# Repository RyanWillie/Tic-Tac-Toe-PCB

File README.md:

# Tic-Tac-Toe-PCB

A continuation of my Hobby PCB designs is the arduino based Tic Tac Toe circuit, utilising some surface mount components this circuit was aimed to give some practical experience in implementing a microcontroller from scratch utilising the reference design sheets. Using multiplexing each grid is able to light up with an X or a O to indicate who has claimed the tile.

## Component Selection

The main principle of the component selection was to use readily available components with libraries available for easy and quick setup,as well as preferring breakout boards so that the components can be easily salvaged/replaced for other projects when it is not needed. Therefore the microcontroller will be an Arduino nano, and the popular NRF24L01 transciever as the available libary makes connection extremely easy.

## BOM
  - Arduino Nano
  - 72x LED
  - 9 x Switches
  - Crystal
  - Capacitors
  
## Proof of Concept
 No proof of concept was able to be created for this circuit due to the required components that were not on hand.

## PCB Design and Manufacturing

The open source program KiCad was used as the design software for the PCB, it is a 2 layer board designed to meet JLCPCB's requirements. As the board is a one off the space and shape requirements are purely to achieve the smallest practical footprint.

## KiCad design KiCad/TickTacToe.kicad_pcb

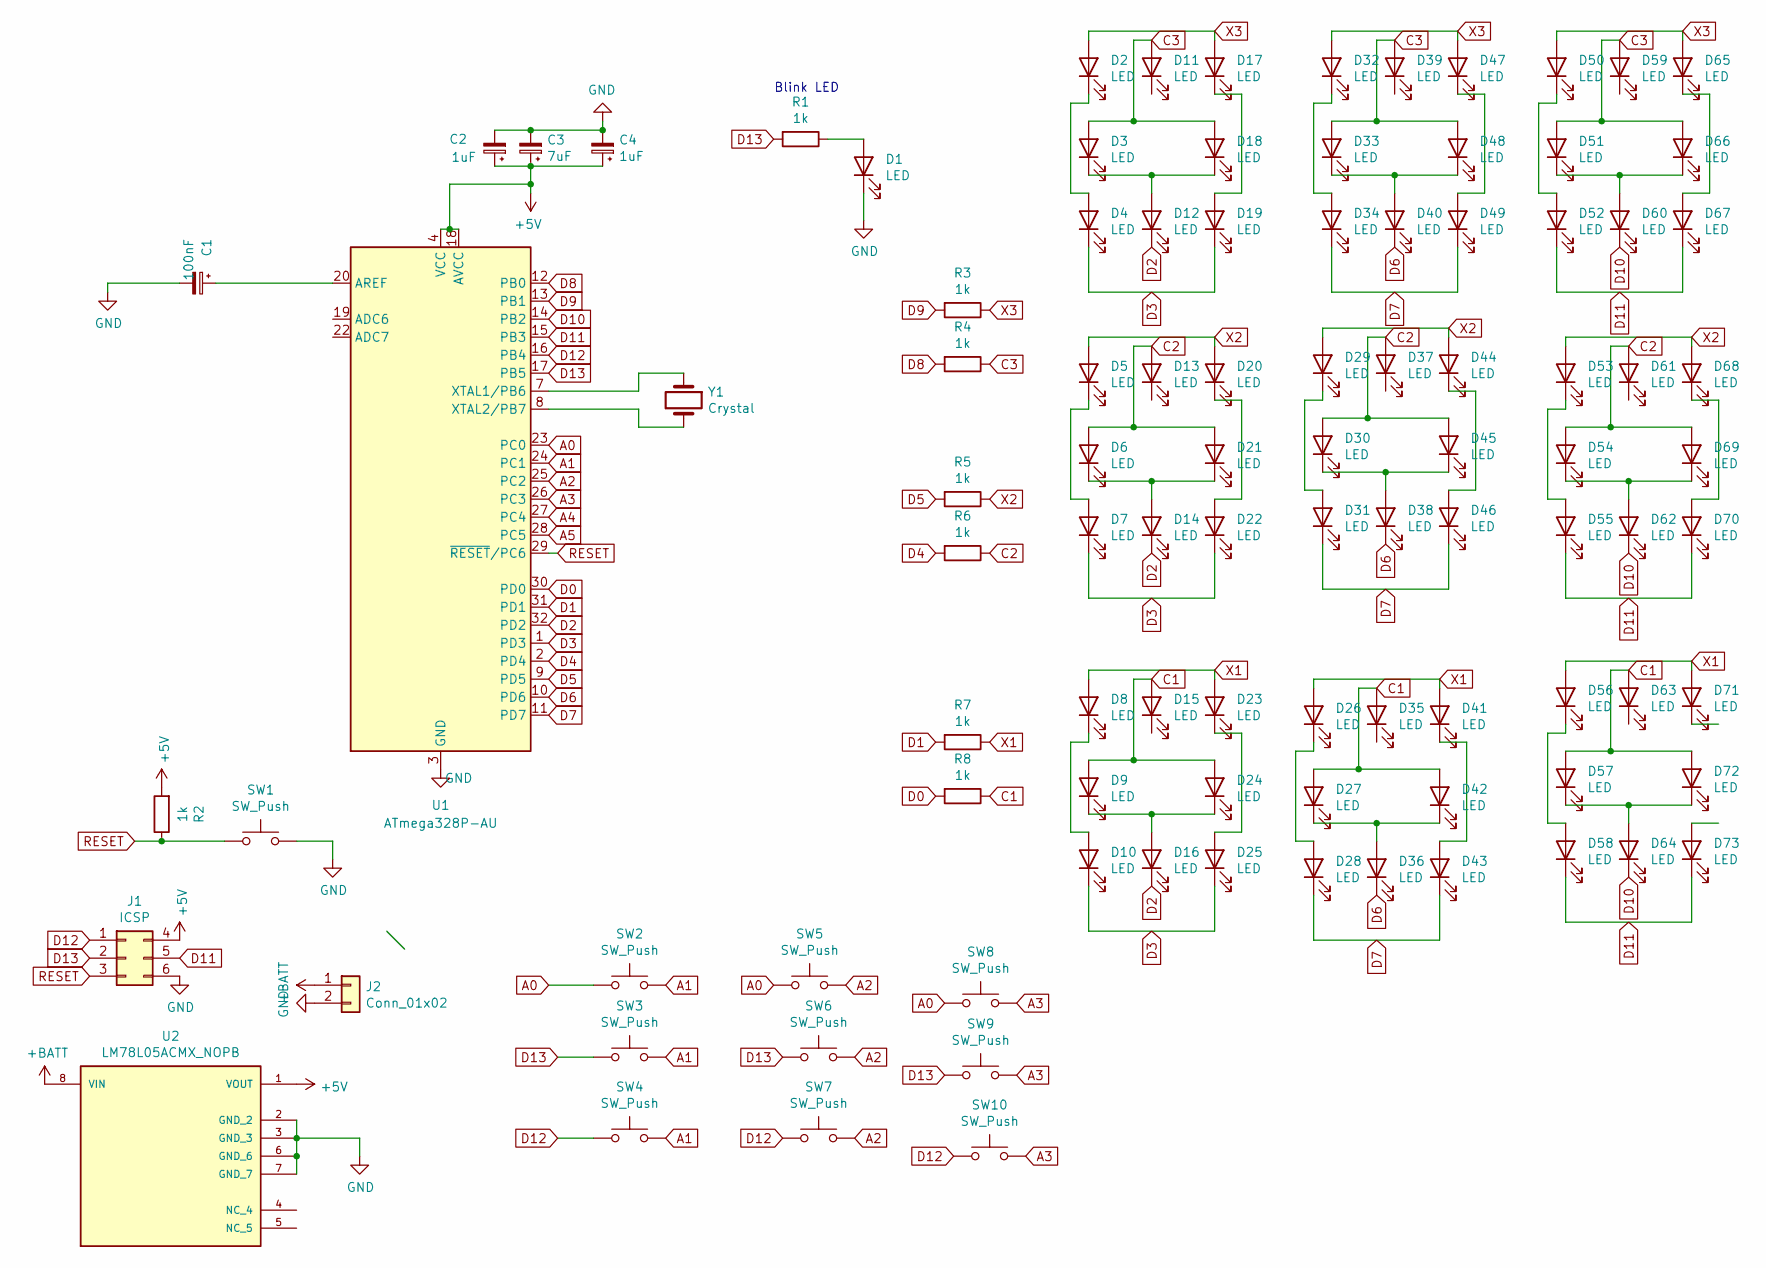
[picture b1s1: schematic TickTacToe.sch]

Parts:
C1: 100nF; CP_Radial_Tantal_D8.0mm_P5.00mm
C2, C4: 1uF; CP_Radial_Tantal_D8.0mm_P5.00mm
C3: 7uF; CP_Radial_Tantal_D8.0mm_P5.00mm
D1, D2, D3, D4, D5, D6, D7, D8, D9, D10, D11, D12, D13, D14, D15, D16, D17, D18, D19, D20, D21, D22, D23, D24, D25, D26, D27, D28, D29, D30, D31, D32, D33, D34, D35, D36, D37, D38, D39, D40, D41, D42, D43, D44, D45, D46, D47, D48, D49, D50, D51, D52, D53, D54, D55, D56, D57, D58, D59, D60, D61, D62, D63, D64, D65, D66, D67, D68, D69, D70, D71, D72, D73: LED; LED_D5.0mm
J1: ICSP; PinHeader_2x03_P1.00mm_Vertical
J2: Conn_01x02; PinHeader_1x02_P1.00mm_Vertical
R1, R2, R3, R4, R5, R6, R7, R8: 1k; R_Axial_DIN0204_L3.6mm_D1.6mm_P2.54mm_Vertical
SW1, SW2, SW3, SW4, SW5, SW6, SW7, SW8, SW9, SW10: SW_Push; SW_1825910-6-4
U1: ATmega328P-AU; TQFP-32_7x7mm_P0.8mm
U2: LM78L05ACMX_NOPB; SOIC127P599X175-8N; PARTREV L
Y1: Crystal; Crystal_HC49-4H_Vertical

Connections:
+5V: C2.1, C3.1, C4.1, J1.4, R2.2, U1.4 (VCC), U1.6 (VCC), U1.18 (AVCC), U2.1 (VOUT)
+BATT: J2.1, U2.8 (VIN)
A0: SW2.1, SW5.1, SW8.1, U1.23 (PC0)
A1: SW2.2, SW3.2, SW4.2, U1.24 (PC1)
A2: SW5.2, SW6.2, SW7.2, U1.25 (PC2)
A3: SW8.2, SW9.2, SW10.2, U1.26 (PC3)
A4: U1.27 (PC4)
A5: U1.28 (PC5)
C1: D9.2 (A), D15.2 (A), D24.2 (A), D27.2 (A), D35.2 (A), D42.2 (A), D57.2 (A), D63.2 (A), D72.2 (A), R8.1
C2: D6.2 (A), D13.2 (A), D21.2 (A), D30.2 (A), D37.2 (A), D45.2 (A), D54.2 (A), D61.2 (A), D69.2 (A), R6.1
C3: D3.2 (A), D11.2 (A), D18.2 (A), D33.2 (A), D39.2 (A), D48.2 (A), D51.2 (A), D59.2 (A), D66.2 (A), R4.1
D0: R8.2, U1.30 (PD0)
D1: R7.2, U1.31 (PD1)
D2: D12.1 (K), D14.1 (K), D16.1 (K), U1.32 (PD2)
D3: D4.1 (K), D7.1 (K), D10.1 (K), D19.1 (K), D22.1 (K), D25.1 (K), U1.1 (PD3)
D4: R6.2, U1.2 (PD4)
D5: R5.2, U1.9 (PD5)
D6: D36.1 (K), D38.1 (K), D40.1 (K), U1.10 (PD6)
D7: D28.1 (K), D31.1 (K), D34.1 (K), D43.1 (K), D46.1 (K), D49.1 (K), U1.11 (PD7)
D8: R4.2, U1.12 (PB0)
D9: R3.2, U1.13 (PB1)
D10: D60.1 (K), D62.1 (K), D64.1 (K), U1.14 (PB2)
D11: D52.1 (K), D55.1 (K), D58.1 (K), D67.1 (K), D70.1 (K), D73.1 (K), J1.5, U1.15 (PB3)
D12: J1.1, SW4.1, SW7.1, SW10.1, U1.16 (PB4)
D13: J1.2, R1.2, SW3.1, SW6.1, SW9.1, U1.17 (PB5)
GND: C1.2, C2.2, C3.2, C4.2, D1.1 (K), J1.6, J2.2, SW1.2, U1.3 (GND), U1.5 (GND), U1.21 (GND), U2.2 (GND_2), U2.3 (GND_3), U2.6 (GND_6), U2.7 (GND_7)
unnamed: C1.1, U1.20 (AREF)
unnamed: D1.2 (A), R1.1
unnamed: D2.1 (K), D4.2 (A)
unnamed: D5.1 (K), D7.2 (A)
unnamed: D8.1 (K), D10.2 (A)
unnamed: D3.1 (K), D12.2 (A), D18.1 (K)
unnamed: D6.1 (K), D14.2 (A), D21.1 (K)
unnamed: D9.1 (K), D16.2 (A), D24.1 (K)
unnamed: D17.1 (K), D19.2 (A)
unnamed: D20.1 (K), D22.2 (A)
unnamed: D23.1 (K), D25.2 (A)
unnamed: D26.1 (K), D28.2 (A)
unnamed: D27.1 (K), D36.2 (A), D42.1 (K)
unnamed: D29.1 (K), D31.2 (A)
unnamed: D30.1 (K), D38.2 (A), D45.1 (K)
unnamed: D32.1 (K), D34.2 (A)
unnamed: D33.1 (K), D40.2 (A), D48.1 (K)
unnamed: D41.1 (K), D43.2 (A)
unnamed: D44.1 (K), D46.2 (A)
unnamed: D47.1 (K), D49.2 (A)
unnamed: D50.1 (K), D52.2 (A)
unnamed: D51.1 (K), D60.2 (A), D66.1 (K)
unnamed: D53.1 (K), D55.2 (A)
unnamed: D54.1 (K), D62.2 (A), D69.1 (K)
unnamed: D56.1 (K), D58.2 (A)
unnamed: D57.1 (K), D64.2 (A), D72.1 (K)
unnamed: D65.1 (K), D67.2 (A)
unnamed: D68.1 (K), D70.2 (A)
unnamed: U1.7 (XTAL1/PB6), Y1.1
unnamed: U1.8 (XTAL2/PB7), Y1.2
RESET: J1.3, R2.1, SW1.1, U1.29 (~RESET~/PC6)
X1: D8.2 (A), D23.2 (A), D26.2 (A), D41.2 (A), D56.2 (A), D71.2 (A), R7.1
X2: D5.2 (A), D20.2 (A), D29.2 (A), D44.2 (A), D53.2 (A), D68.2 (A), R5.1
X3: D2.2 (A), D17.2 (A), D32.2 (A), D47.2 (A), D50.2 (A), D65.2 (A), R3.1

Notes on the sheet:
Blink LED

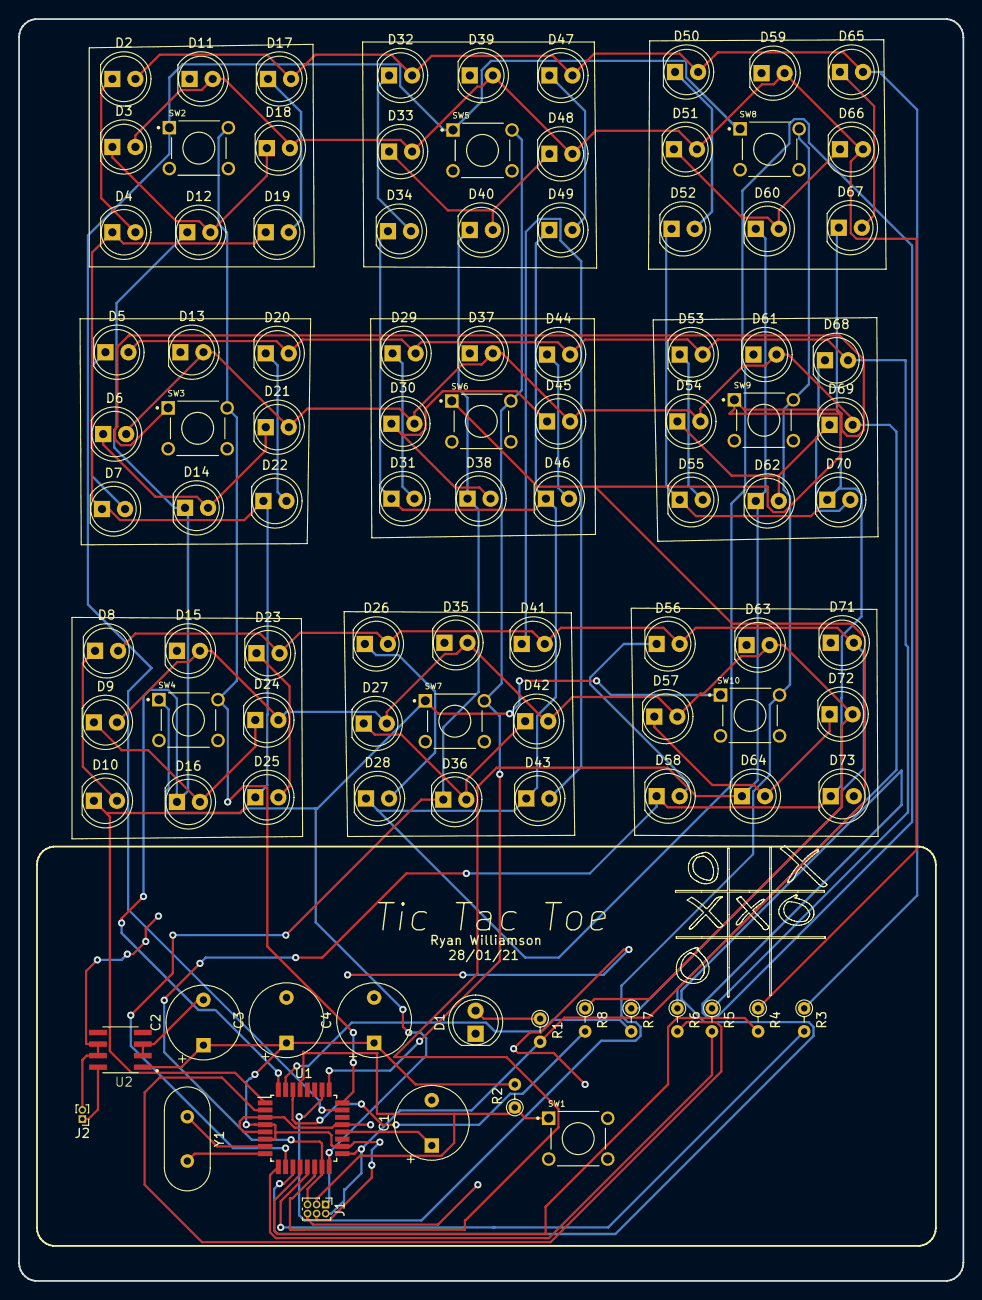
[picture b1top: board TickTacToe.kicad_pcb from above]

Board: 2 copper layers, 104.0 x 139.0 mm, 100 parts (0 on the bottom side), 58 nets.

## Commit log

2021-02-06 KiCad design files, schematic and render images
2021-02-06 Updating ReadMe with project information
